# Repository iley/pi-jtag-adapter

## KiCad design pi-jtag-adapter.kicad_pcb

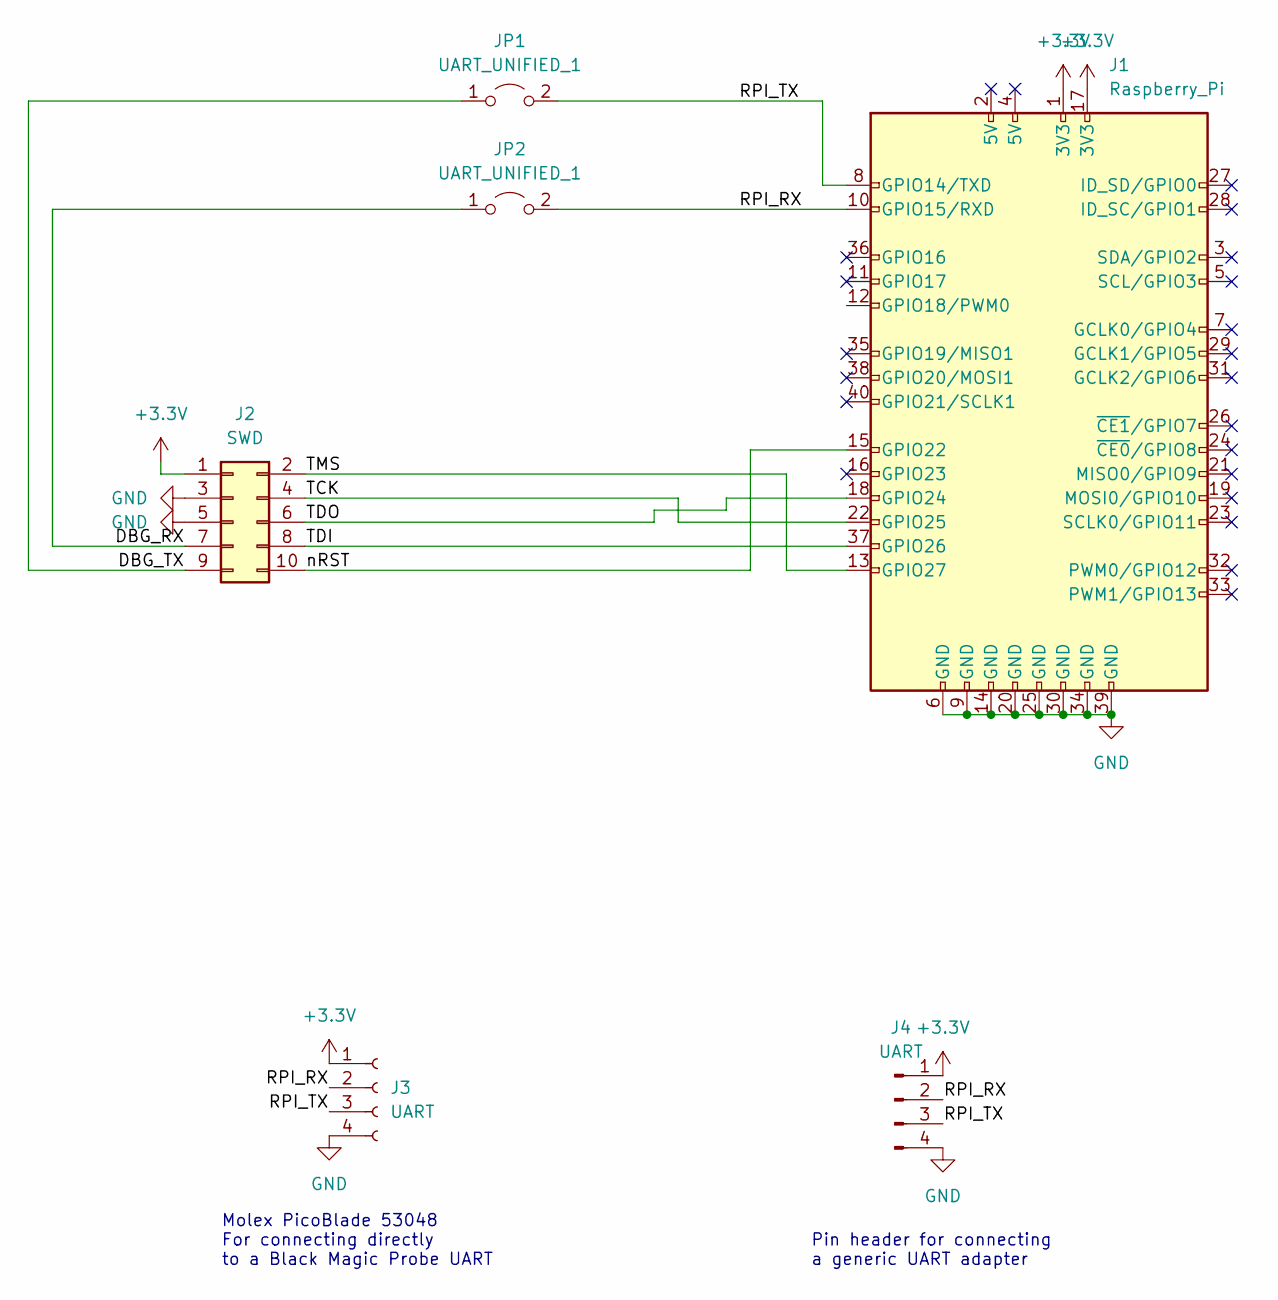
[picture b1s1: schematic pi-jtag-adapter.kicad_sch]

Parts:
J1: Raspberry_Pi; PinHeader_2x20_P2.54mm_Vertical
J2: SWD; PinHeader_2x05_P1.27mm_Vertical
J3: UART; Molex_PicoBlade_53048-0410_1x04_P1.25mm_Horizontal
J4: UART; PinHeader_1x04_P2.54mm_Vertical
JP1, JP2: UART_UNIFIED_1; SolderJumper-2_P1.3mm_Open_TrianglePad1.0x1.5mm

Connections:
+3.3V: J1.1 (3V3), J1.17 (3V3), J2.1, J3.1, J4.1
/DBG_RX: J2.7, JP2.1 (A)
/DBG_TX: J2.9, JP1.1 (A)
/RPI_RX: J1.10 (GPIO15/RXD), J3.2, J4.2, JP2.2 (B)
/RPI_TX: J1.8 (GPIO14/TXD), J3.3, J4.3, JP1.2 (B)
/TCK: J1.22 (GPIO25), J2.4
/TDI: J1.37 (GPIO26), J2.8
/TDO: J1.18 (GPIO24), J2.6
/TMS: J1.13 (GPIO27), J2.2
/nRST: J1.15 (GPIO22), J2.10
GND: J1.6 (GND), J1.9 (GND), J1.14 (GND), J1.20 (GND), J1.25 (GND), J1.30 (GND), J1.34 (GND), J1.39 (GND), J2.3, J2.5, J3.4, J4.4

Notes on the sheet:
Molex PicoBlade 53048 For connecting directly to a Black Magic Probe UART
Pin header for connecting a generic UART adapter

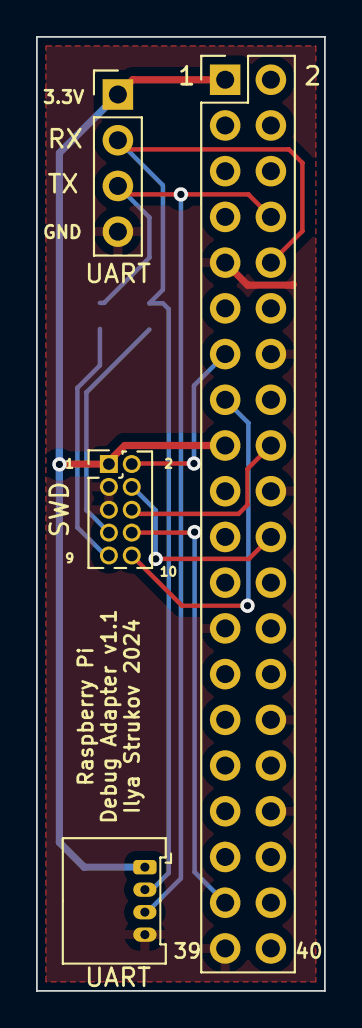
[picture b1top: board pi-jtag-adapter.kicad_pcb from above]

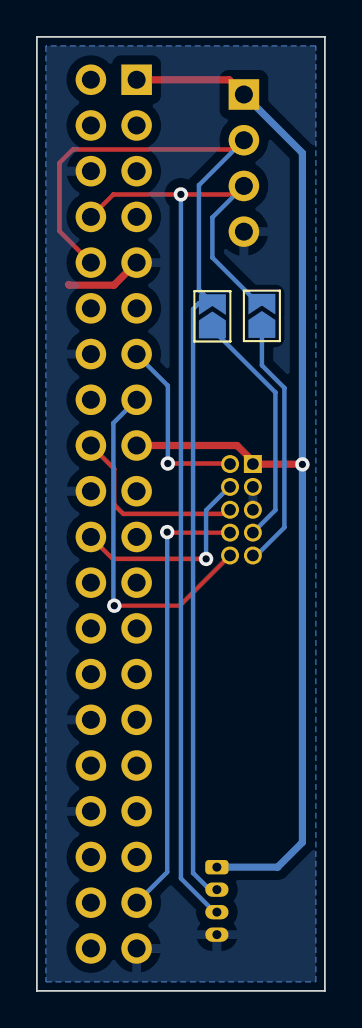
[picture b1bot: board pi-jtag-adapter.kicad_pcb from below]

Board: 2 copper layers, 16.0 x 53.0 mm, 6 parts (2 on the bottom side), 11 nets.

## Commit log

2024-03-10 Fix the layout
2024-03-10 Fix schematic and PCB layout
2024-03-16 Upgrade to the last Kicad version
